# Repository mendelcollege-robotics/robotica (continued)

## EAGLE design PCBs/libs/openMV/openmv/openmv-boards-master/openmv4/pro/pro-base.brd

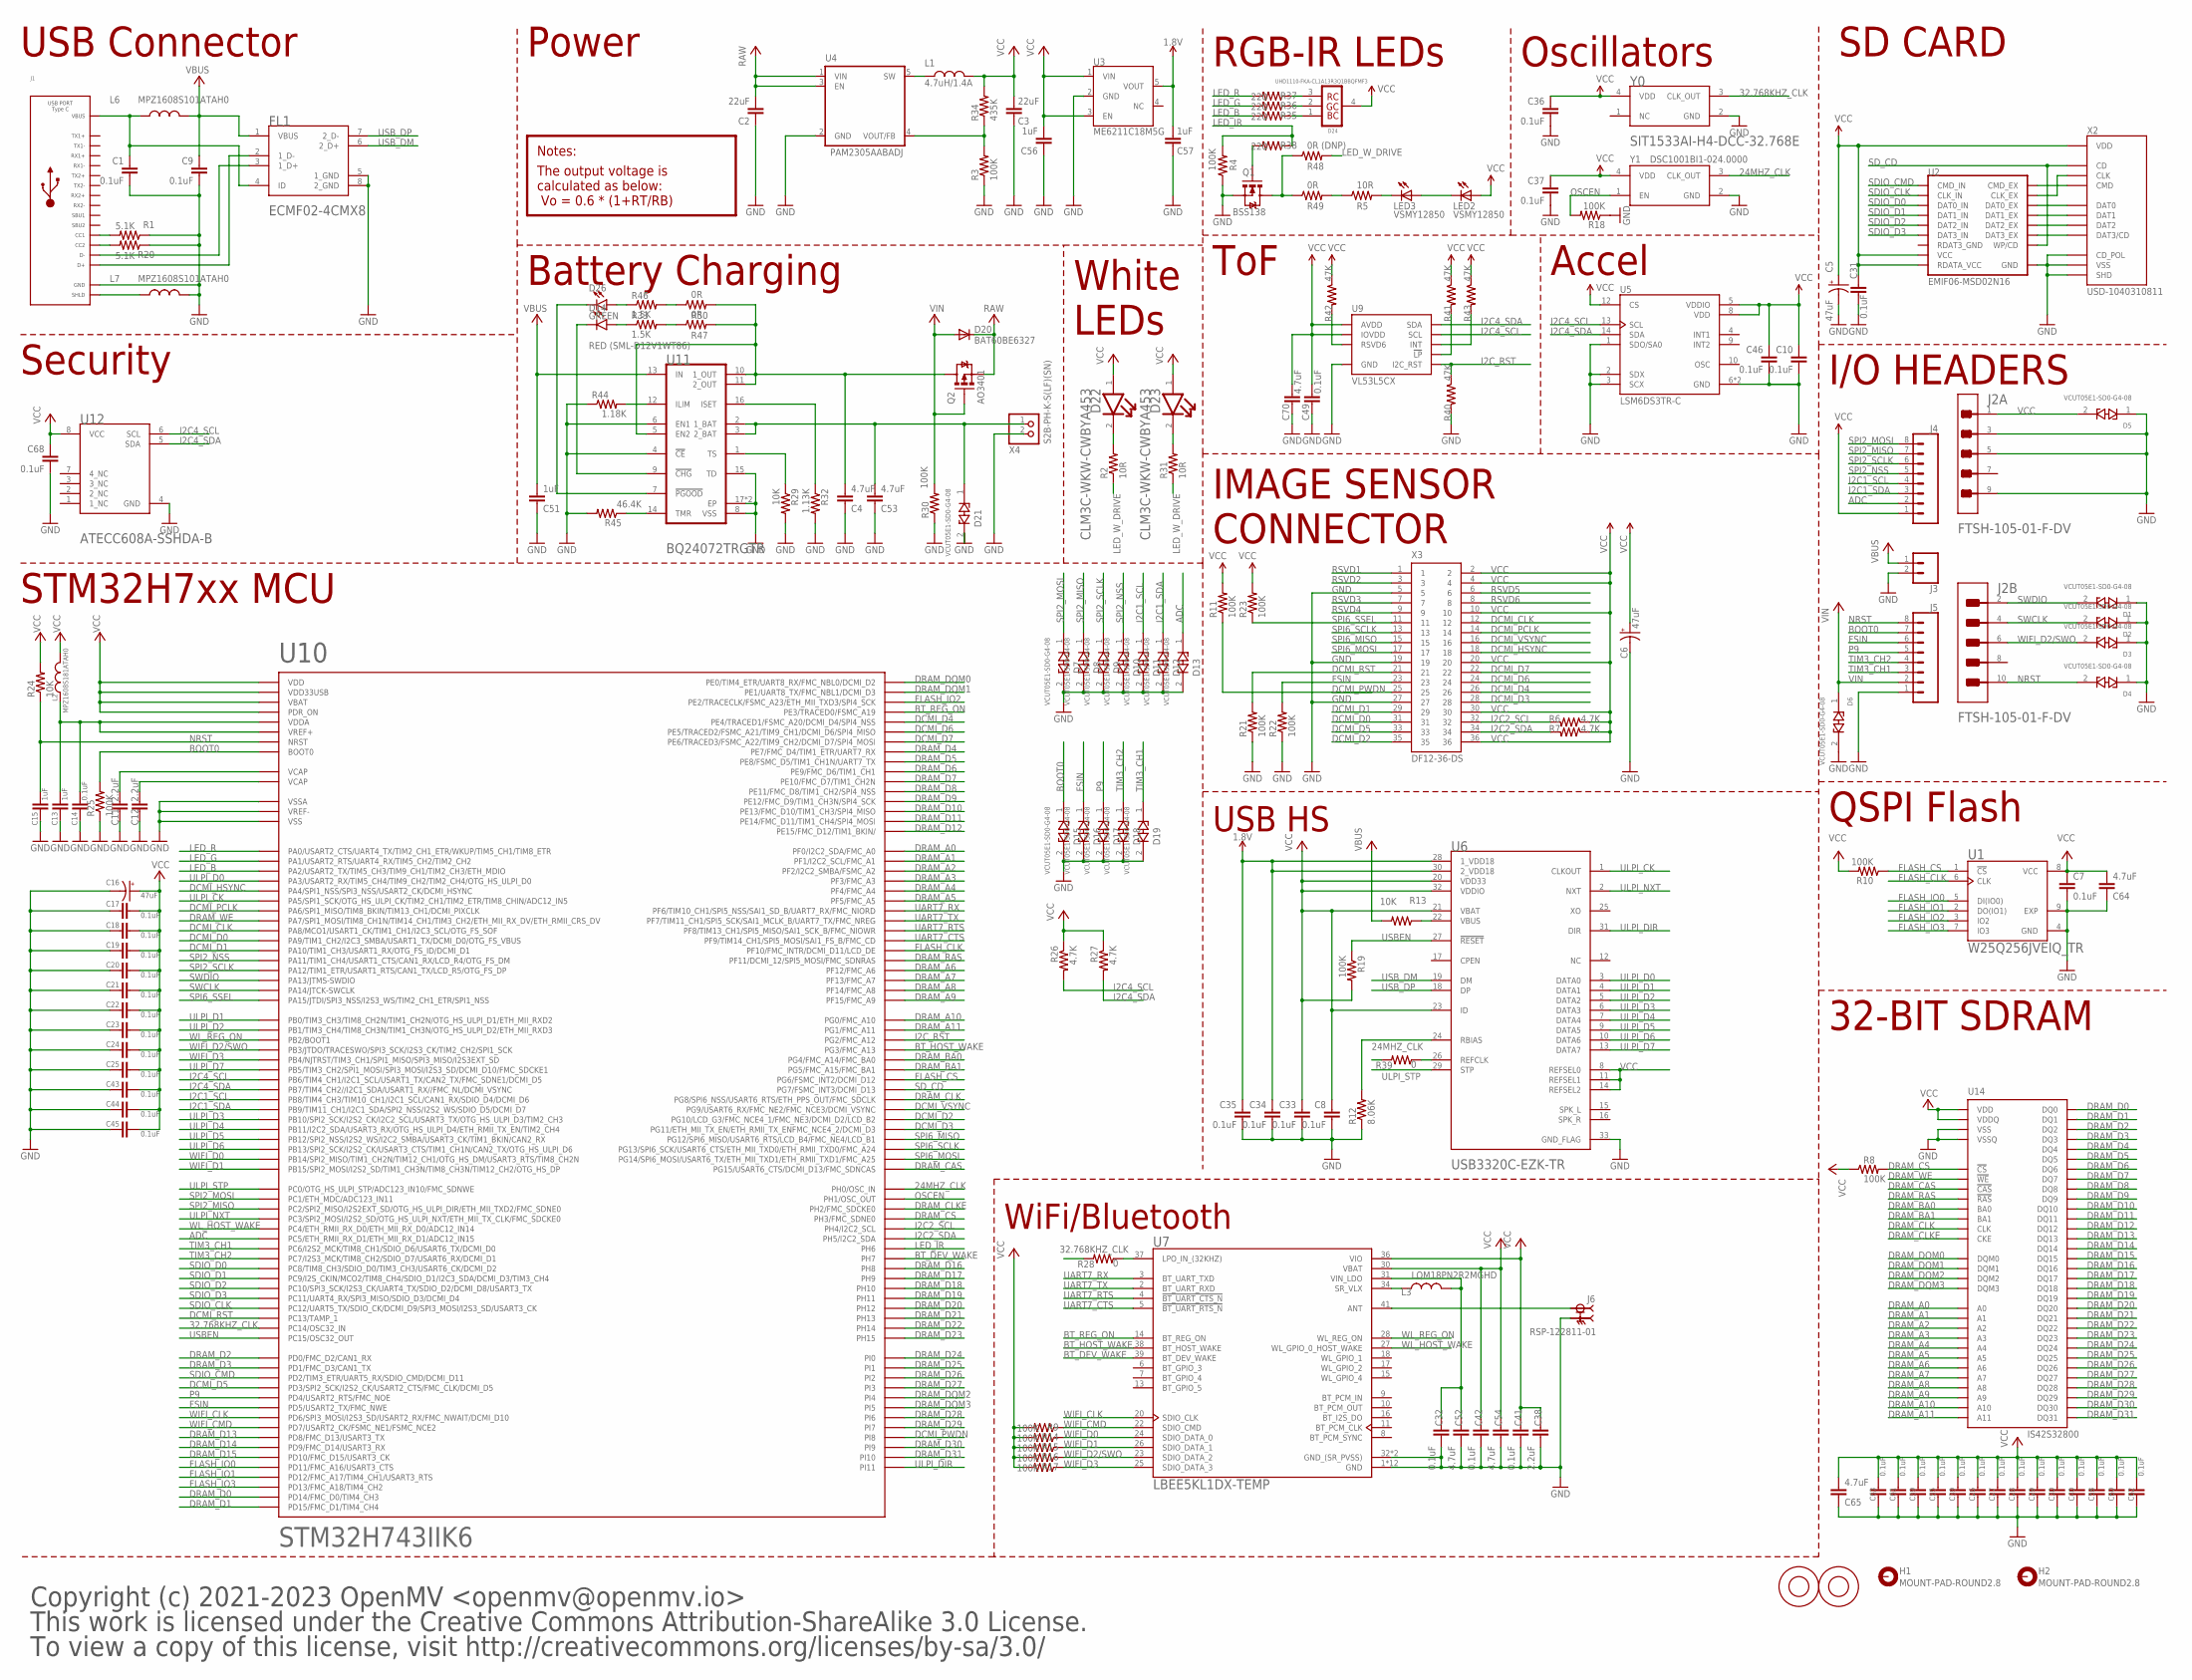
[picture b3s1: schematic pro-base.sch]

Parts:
C1, C7, C8, C9, C10, C14, C31, C32, C33, C34, C35, C36, C37, C41, C42, C46, C49, C68: 0.1uF; 0402-CAP
C2, C3: 22uF; 0805
C4, C52, C53, C54, C64, C65, C70: 4.7uF; 0603
C5, C6, C16: 47uF; EIA3216
C11, C12, C38: 2.2uF; 0402-CAP
C13, C15, C51, C56, C57: 1uF; 0402-CAP
C17, C18, C19, C20, C21, C22, C23, C24, C25, C26, C27, C28, C29, C30, C39, C40, C43, C44, C45, C55, C58, C59, C60, C61, C62, C63: 0.1uF; C0201
D1, D2, D3, D4, D5, D6, D7, D8, D9, D10, D11, D12, D13, D15, D16, D17, D18, D19, D21: VISHAY_VCUT05E1-SD0-G4-08VISHAY_VCUT05E1-SD0-G4-0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; VISHAY_VCUT05E1-SD0-G4-08_0
D14: RED (SML-D12V1WT86); LED-0603
D20: BAT60BE6327; SOD-323
D22, D23: CREE_CLM3C-WKW-CWBYA453CREE_CLM3C-WKW-CWBYA453_0_0; CREE_CLM3C-WKW-CWBYA453_0
D24: CREE_UHD1110-FKA-CL1A13R3Q1BBQFMF3CREE_UHD1110-FK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; CREE_UHD1110-FKA-CL1A13R3Q1BBQFMF3_0
D26: GREEN; LED-0603
FL1: STMICROELECTRONICS_ECMF02-4CMX8STMICROELECTRONICS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; STMICROELECTRONICS_ECMF02-4CMX8_0
H1, H2: MOUNT-PAD-ROUND2.8; 2,8-PAD
J1: USB_TYPE-C_105450-0101; 105450-0101
J2: SAMTEC_FTSH-105-01-F-DVSAMTEC_FTSH-105-01-F-DV_0_0; SAMTEC_FTSH-105-01-F-DV_0
J3: CONN_02; 1X02
J4, J5: CONN_08"; 1X08
J6: RSP-122811-01; SAMTEC_RSP-122811-01
L1: 4.7uH/1.4A; 1007
L2: MPZ1608S181ATAH0; C0402
L3: LQM18PN2R2MGHD; 0603
L6, L7: MPZ1608S101ATAH0; C0402
LED2, LED3: VSMY12850; LED-1206
M1, M2: 9774030243R; 9774030151R
Q1: BSS138; SOT23-3
Q2: AO3401; SOT23-3
R1, R20: 5.1K; 0402-RES
R2, R5, R31: 10R; 0402-RES
R3, R4, R8, R9, R10, R11, R14, R15, R16, R17, R18, R19, R21, R22, R23, R25, R30: 100K; 0402-RES
R6, R7, R26, R27: 4.7K; 0402-RES
R12: 8.06K; 0402-RES
R13, R24, R29: 10K; 0402-RES
R28, R39: 0; 0402-RES
R32: 1.13K; 0402-RES
R33, R46: 1.5K; 0402-RES
R34: 435K; 0402-RES
R35, R36, R37, R38: 220; 0402-RES
R40, R41, R42, R43: 47K; 0402-RES
R44: 1.18K; 0402-RES
R45: 46.4K; 0402-RES
R47, R49, R50: 0R; 0402-RES
R48: 0R (DNP); 0402-RES
U1: W25Q256JVEIQ_TR; SON127P800X600X80-9N
U2: EMIF06-MSD02N16; QFN3.5
U3: ME6211C18M5G; SOT23-5
U4: PAM2305AABADJ; TSOT25
U5: LSM6DS3TR-C; PQFN50P300X250X86-14N
U6: MICROCHIP_USB3320C-EZK-TRMICROCHIP_USB3320C-EZK-T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; MICROCHIP_USB3320C-EZK-TR_1
U7: LBEE5KL1DX-TEMP; XCVR_LBEE5KL1DX-TEMP
U9: VL53L5CX
U10: STM32H743IIK6; UFGBGA-176
U11: TEXAS_INSTRUMENTS_BQ24072TRGTRTEXAS_INSTRUMENTS_B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; TEXAS_INSTRUMENTS_BQ24072TRGTR_0
U12: MICROCHIP_ATECC608A-SSHDA-BMICROCHIP_ATECC608A-SS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; MICROCHIP_ATECC608A-SSHDA-B_0
U14: IS42S32800; BGA90
X2: USD-1040310811; 1040310811
X3: DF12-36-DS
X4: S2B-PH-K-S(LF)(SN); JST-PH-2-THM-RA
Y0: SITIME_SIT1533AI-H4-DCC-32.768ESITIME_SIT1533AI-H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; SITIME_SIT1533AI-H4-DCC-32.768E_0
Y1: DSC1001BI1-024.0000; OSC_DSC6083CI2A-032K768

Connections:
1.8V: C34.1, C35.1, C57.2, U3.5 (VOUT), U6.28 (1_VDD18), U6.30 (2_VDD18)
24MHZ_CLK: R39.2, U10.G1 (PH0/OSC_IN), Y1.3 (CLK_OUT)
32.768KHZ_CLK: R28.2, U10.E1 (PC14/OSC32_IN), Y0.3 (CLK_OUT)
ADC: D13.1, J4.2, U10.P5 (PC5/ETH_RMII_RX_D1/ETH_MII_RX_D1/ADC12_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)
ANT_PI_I: J6.1, U7.41 (ANT)
BAT: C53.2, D21.1, U11.2 (1_BAT), U11.3 (2_BAT), X4.1 (2)
BOOT0: D15.1, J5.7, R25.2, U10.D6 (BOOT0)
BT_DEV_WAKE: U7.39 (BT_DEV_WAKE), U10.N12 (PH7)
BT_HOST_WAKE: U7.38 (BT_HOST_WAKE), U10.K15 (PG3/FMC_A13)
BT_REG_ON: U7.14 (BT_REG_ON), U10.A1 (PE3/TRACED0/FSMC_A19)
CC1: J1.A5 (CC1), R1.2
CC2: J1.B5 (CC2), R20.2
CHG: D14.C, U11.9 (!CHG!)
CLK: U2.P$11 (CLK_EX), X2.P$5 (CLK)
CMD: U2.P$12 (CMD_EX), X2.P$3 (CMD)
DAT0: U2.P$10 (DAT0_EX), X2.P$7 (DAT0)
DAT1: U2.P$9 (DAT1_EX), X2.P$8 (DAT1)
DAT2: U2.P$14 (DAT2_EX), X2.P$1 (DAT2)
DAT3: U2.P$13 (DAT3_EX), X2.P$2 (DAT3/CD)
DCMI_CLK: U10.F15 (PA8/MCO1/USART1_CK/TIM1_CH1/I2C3_SCL/OT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), X3.12
DCMI_D0: U10.E15 (PA9/TIM1_CH2/I2C3_SMBA/USART1_TX/DCMI_D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), X3.31
DCMI_D1: U10.D15 (PA10/TIM1_CH3/USART1_RX/OTG_FS_ID/DCMI_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), X3.29
DCMI_D2: U10.B10 (PG10/LCD_G3/FMC_NCE4_1/FMC_NE3/DCMI_D2/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), X3.35
DCMI_D3: U10.B9 (PG11/ETH_MII_TX_EN/ETH_RMII_TX_ENFMC_NC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), X3.28
DCMI_D4: U10.B1 (PE4/TRACED1/FSMC_A20/DCMI_D4/SPI4_NSS), X3.26
DCMI_D5: U10.D11 (PD3/SPI2_SCK/I2S2_CK/USART2_CTS/FMC_CLK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), X3.33
DCMI_D6: U10.B2 (PE5/TRACED2/FSMC_A21/TIM9_CH1/DCMI_D6/S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), X3.24
DCMI_D7: U10.B3 (PE6/TRACED3/FSMC_A22/TIM9_CH2/DCMI_D7/S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), X3.22
DCMI_HSYNC: U10.N4 (PA4/SPI1_NSS/SPI3_NSS/USART2_CK/DCMI_HS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), X3.18
DCMI_PCLK: U10.P3 (PA6/SPI1_MISO/TIM8_BKIN/TIM13_CH1/DCMI_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), X3.14
DCMI_PWDN: R11.1, U10.D2 (PI8), X3.25
DCMI_RST: R21.2, U10.D1 (PC13/TAMP_1), X3.21
DCMI_VSYNC: U10.C10 (PG9/USART6_RX/FMC_NE2/FMC_NCE3/DCMI_VSY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), X3.16
DN: FL1.3 (1_D+), J1.A7 (D-), J1.B7 (D-)
DP: FL1.2 (1_D-), J1.A6 (D+), J1.B6 (D+)
DRAM_A0: U10.E2 (PF0/I2C2_SDA/FMC_A0), U14.G8 (A0)
DRAM_A1: U10.H3 (PF1/I2C2_SCL/FMC_A1), U14.G9 (A1)
DRAM_A2: U10.H2 (PF2/I2C2_SMBA/FSMC_A2), U14.F7 (A2)
DRAM_A3: U10.J2 (PF3/FMC_A3), U14.F3 (A3)
DRAM_A4: U10.J3 (PF4/FMC_A4), U14.G1 (A4)
DRAM_A5: U10.K3 (PF5/FMC_A5), U14.G2 (A5)
DRAM_A6: U10.P6 (PF12/FMC_A6), U14.G3 (A6)
DRAM_A7: U10.N6 (PF13/FMC_A7), U14.H1 (A7)
DRAM_A8: U10.R7 (PF14/FMC_A8), U14.H2 (A8)
DRAM_A9: U10.P7 (PF15/FMC_A9), U14.J3 (A9)
DRAM_A10: U10.N7 (PG0/FMC_A10), U14.G7 (A10)
DRAM_A11: U10.M7 (PG1/FMC_A11), U14.H9 (A11)
DRAM_BA0: U10.K14 (PG4/FMC_A14/FMC_BA0), U14.J7 (BA0)
DRAM_BA1: U10.K13 (PG5/FMC_A15/FMC_BA1), U14.H8 (BA1)
DRAM_CAS: U10.B7 (PG15/USART6_CTS/DCMI_D13/FMC_SDNCAS), U14.K7 (!CAS)
DRAM_CLK: U10.H14 (PG8/SPI6_NSS/USART6_RTS/ETH_PPS_OUT/FMC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), U14.J1 (CLK)
DRAM_CLKE: U10.F4 (PH2/FMC_SDCKE0), U14.J2 (CKE)
DRAM_CS: R8.2, U10.G4 (PH3/FMC_SDNE0), U14.J8 (!CS)
DRAM_D0: U10.M14 (PD14/FMC_D0/TIM4_CH3), U14.R8 (DQ0)
DRAM_D1: U10.L14 (PD15/FMC_D1/TIM4_CH4), U14.N7 (DQ1)
DRAM_D2: U10.B12 (PD0/FMC_D2/CAN1_RX), U14.R9 (DQ2)
DRAM_D3: U10.C12 (PD1/FMC_D3/CAN1_TX), U14.N8 (DQ3)
DRAM_D4: U10.R8 (PE7/FMC_D4/TIM1_ETR/UART7_RX), U14.P9 (DQ4)
DRAM_D5: U10.P8 (PE8/FSMC_D5/TIM1_CH1N/UART7_TX), U14.M8 (DQ5)
DRAM_D6: U10.P9 (PE9/FMC_D6/TIM1_CH1), U14.M7 (DQ6)
DRAM_D7: U10.R9 (PE10/FMC_D7/TIM1_CH2N), U14.L8 (DQ7)
DRAM_D8: U10.P10 (PE11/FMC_D8/TIM1_CH2/SPI4_NSS), U14.L2 (DQ8)
DRAM_D9: U10.R10 (PE12/FMC_D9/TIM1_CH3N/SPI4_SCK), U14.M3 (DQ9)
DRAM_D10: U10.N11 (PE13/FMC_D10/TIM1_CH3/SPI4_MISO), U14.M2 (DQ10)
DRAM_D11: U10.P11 (PE14/FMC_D11/TIM1_CH4/SPI4_MOSI), U14.P1 (DQ11)
DRAM_D12: U10.R11 (PE15/FMC_D12/TIM1_BKIN/), U14.N2 (DQ12)
DRAM_D13: U10.P15 (PD8/FMC_D13/USART3_TX), U14.R1 (DQ13)
DRAM_D14: U10.P14 (PD9/FMC_D14/USART3_RX), U14.N3 (DQ14)
DRAM_D15: U10.N15 (PD10/FMC_D15/USART3_CK), U14.R2 (DQ15)
DRAM_D16: U10.M12 (PH8), U14.E8 (DQ16)
DRAM_D17: U10.M13 (PH9), U14.D7 (DQ17)
DRAM_D18: U10.L13 (PH10), U14.D8 (DQ18)
DRAM_D19: U10.L12 (PH11), U14.B9 (DQ19)
DRAM_D20: U10.K12 (PH12), U14.C8 (DQ20)
DRAM_D21: U10.E12 (PH13), U14.A9 (DQ21)
DRAM_D22: U10.E13 (PH14), U14.C7 (DQ22)
DRAM_D23: U10.D13 (PH15), U14.A8 (DQ23)
DRAM_D24: U10.E14 (PI0), U14.A2 (DQ24)
DRAM_D25: U10.D14 (PI1), U14.C3 (DQ25)
DRAM_D26: U10.C14 (PI2), U14.A1 (DQ26)
DRAM_D27: U10.C13 (PI3), U14.C2 (DQ27)
DRAM_D28: U10.C3 (PI6), U14.B1 (DQ28)
DRAM_D29: U10.C2 (PI7), U14.D2 (DQ29)
DRAM_D30: U10.D3 (PI9), U14.D3 (DQ30)
DRAM_D31: U10.E3 (PI10), U14.E2 (DQ31)
DRAM_DQM0: U10.A4 (PE0/TIM4_ETR/UART8_RX/FMC_NBL0/DCMI_D2), U14.K9 (DQM0)
DRAM_DQM1: U10.A3 (PE1/UART8_TX/FMC_NBL1/DCMI_D3), U14.K1 (DQM1)
DRAM_DQM2: U10.D4 (PI4), U14.F8 (DQM2)
DRAM_DQM3: U10.C4 (PI5), U14.F2 (DQM3)
DRAM_RAS: U10.R6 (PF11/DCMI_12/SPI5_MOSI/FMC_SDNRAS), U14.J9 (!RAS)
DRAM_WE: U10.R3 (PA7/SPI1_MOSI/TIM8_CH1N/TIM14_CH1/TIM3_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), U14.K8 (!WE)
FB: R3.2, R34.1, U4.4 (VOUT/FB)
FLASH_CLK: U1.6 (CLK), U10.L1 (PF10/FMC_INTR/DCMI_D11/LCD_DE)
FLASH_CS: R10.1, U1.1 (!CS), U10.J15 (PG6/FSMC_INT2/DCMI_D12)
FLASH_IO0: U1.5 (DI(IO0)), U10.N14 (PD11/FMC_A16/USART3_CTS)
FLASH_IO1: U1.2 (DO(IO1)), U10.N13 (PD12/FMC_A17/TIM4_CH1/USART3_RTS)
FLASH_IO2: U1.3 (IO2), U10.A2 (PE2/TRACECLK/FSMC_A23/ETH_MII_TXD3/SPI4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)
FLASH_IO3: U1.7 (IO3), U10.M15 (PD13/FMC_A18/TIM4_CH2)
FSIN: D16.1, J5.6, R22.2, U10.C11 (PD5/USART2_TX/FMC_NWE), X3.23
GND: C1.2, C2.1, C3.1, C4.1, C5.C (-), C6.C (-), C7.2, C8.2, C9.2, C10.2, C11.2, C12.2, C13.2, C14.2, C15.2, C16.C (-), C17.2, C18.2, C19.2, C20.2, C21.2, C22.2, C23.2, C24.2, C25.2, C26.2, C27.2, C28.2, C29.2, C30.2, C31.2, C32.2, C33.2, C34.2, C35.2, C36.2, C37.2, C38.2, C39.2, C40.2, C41.2, C42.2, C43.2, C44.2, C45.2, C46.2, C49.2, C51.1, C52.2, C53.1, C54.2, C55.2, C56.1, C57.1, C58.2, C59.2, C60.2, C61.2, C62.2, C63.2, C64.1, C65.1, C68.2, C70.1, D1.1, D2.1, D3.1, D4.1, D5.1, D6.2, D7.2, D8.2, D9.2, D10.2, D11.2, D12.2, D13.2, D15.2, D16.2, D17.2, D18.2, D19.2, D21.2, FL1.5 (1_GND), FL1.8 (2_GND), J1.A1 (GND), J1.A12 (GND), J1.B1 (GND), J1.B12 (GND), J2.3, J2.5, J2.9, J3.2, J5.1, J6.G1 (GND), J6.G2 (GND), L7.2, Q1.2 (S), R1.1, R3.1, R4.1, R12.1, R18.1, R20.1, R21.1, R22.1, R25.1, R29.2, R30.1, R32.2, R40.2, R44.1, R45.2, U1.4 (GND), U1.9 (EXP), U2.GND, U3.2 (GND), U4.2 (GND), U5.1 (SDO/SA0), U5.2 (SDX), U5.3 (SCX), U5.6 (GND), U5.7 (GND), U6.33 (GND_FLAG), U7.1 (GND), U7.12 (GND)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
I2C1_SCL: D11.1, J4.4, U10.A5 (PB8/TIM4_CH3/TIM10_CH1/I2C1_SCL/CAN1_RX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)
I2C1_SDA: D12.1, J4.3, U10.B4 (PB9/TIM11_CH1/I2C1_SDA/SPI2_NSS/I2S2_WS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)
I2C2_SCL: R6.2, U10.H4 (PH4/I2C2_SCL), X3.32
I2C2_SDA: R7.2, U10.J4 (PH5/I2C2_SDA), X3.34
I2C4_SCL: R26.2, U5.13 (SCL), U9.C4 (SCL), U10.B6 (PB6/TIM4_CH1/I2C1_SCL/USART1_TX/CAN2_TX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), U12.6 (SCL)
I2C4_SDA: R27.2, U5.14 (SDA), U9.C3 (SDA), U10.B5 (PB7/TIM4_CH2//I2C1_SDA/USART1_RX//FMC_N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), U12.5 (SDA)
I2C_RST: R40.1, U9.A1 (I2C_RST), U10.L15 (PG2/FMC_A12)
ISET: R32.1, U11.16 (ISET)
LED_B: R35.2, U10.P2 (PA2/USART2_TX/TIM5_CH3/TIM9_CH1/TIM2_CH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)
LED_B_INT: D24.1 (BLUE_CATHODE), R35.1
LED_DRAIN: Q1.3 (D), R48.1, R49.1
LED_G: R36.2, U10.N2 (PA1/USART2_RTS/UART4_RX/TIM5_CH2/TIM2_C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)
LED_G_INT: D24.2 (GREEN_CATHODE), R36.1
LED_IR: R4.2, R38.1, U10.M11 (PH6)
LED_IR_DRIVE: R5.1, R49.2
LED_IR_DRIVE_0: LED3.C, R5.2
LED_IR_DRIVE_1: LED2.C, LED3.A
LED_IR_INT: Q1.1 (G), R38.2
LED_R: R37.2, U10.N3 (PA0/USART2_CTS/UART4_TX/TIM2_CH1_ETR/WK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)
LED_R_INT: D24.3 (RED_CATHODE), R37.1
LED_W_DRIVE: R2.1, R31.1, R48.2
LED_W_DRIVE_0: D22.2 (CATHODE), R2.2
LED_W_DRIVE_1: D23.2 (CATHODE), R31.2
unnamed: D26.A, R46.1
unnamed: R28.1, U7.37 (LPO_IN_(32KHZ))
unnamed: R39.1, U6.26 (REFCLK)
unnamed: R44.2, U11.12 (ILIM)
unnamed: R41.2, U9.A5 (!LP)
unnamed: R42.2, U9.C2 (RSVD6)
unnamed: R43.2, U9.A3 (INT)
unnamed: R45.1, U11.14 (TMR)
unnamed: D26.C, U11.7 (!PGOOD!)
unnamed: D14.A, R33.1
unnamed: R33.2, R47.1
unnamed: R46.2, R50.1
NRST: C15.1, D4.2, J2.10, J5.8, R24.1, U10.J1 (NRST)
OSCEN: R18.2, U10.H1 (PH1/OSC_OUT), Y1.1 (EN)
OUT: C4.2, Q2.3 (D), R47.2, R50.2, U11.5 (EN2), U11.10 (1_OUT), U11.11 (2_OUT)
P9: D17.1, J5.5, U10.D10 (PD4/USART2_RTS/FMC_NOE)
RAW: C2.2, D20.1 (C), Q2.2 (S), U4.1 (VIN), U4.3 (EN)
RBIAS: R12.2, U6.24 (RBIAS)
RSVD1: X3.1
RSVD2: X3.3
RSVD3: X3.7
RSVD4: X3.9
RSVD5: X3.6
RSVD6: X3.8
SDIO_CLK: U2.P$6 (CLK_IN), U10.A12 (PC12/UART5_TX/SDIO_CK/DCMI_D9/SPI3_MOSI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)
SDIO_CMD: U2.P$5 (CMD_IN), U10.D12 (PD2/TIM3_ETR/UART5_RX/SDIO_CMD/DCMI_D11)
SDIO_D0: U2.P$7 (DAT0_IN), U10.G14 (PC8/TIM8_CH3/SDIO_D0/TIM3_CH3/USART6_CK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)
SDIO_D1: U2.P$8 (DAT1_IN), U10.F14 (PC9/I2S_CKIN/MCO2/TIM8_CH4/SDIO_D1/I2C3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)
SDIO_D2: U2.P$3 (DAT2_IN), U10.B14 (PC10/SPI3_SCK/I2S3_CK/UART4_TX/SDIO_D2/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)
SDIO_D3: U2.P$4 (DAT3_IN), U10.B13 (PC11/UART4_RX/SPI3_MISO/SDIO_D3/DCMI_D4)
SD_CD: U2.P$1 (WP/CD), U10.J14 (PG7/FSMC_INT3/DCMI_D13), X2.CD$1 (CD)
SHIELD_INT: J1.S_T1 (SHLD), J1.S_T2 (SHLD), J1.S_T3 (SHLD), J1.S_T4 (SHLD), L7.1
SPI2_MISO: D8.1, J4.7, U10.M4 (PC2/SPI2_MISO/I2S2EXT_SD/OTG_HS_ULPI_DI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)
SPI2_MOSI: D7.1, J4.8, U10.M3 (PC1/ETH_MDC/ADC123_IN11)
SPI2_NSS: D10.1, J4.5, U10.C15 (PA11/TIM1_CH4/USART1_CTS/CAN1_RX/LCD_R4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)
SPI2_SCLK: D9.1, J4.6, U10.B15 (PA12/TIM1_ETR/USART1_RTS/CAN1_TX/LCD_R5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)
SPI6_MISO: U10.B8 (PG12/SPI6_MISO/USART6_RTS/LCD_B4/FMC_NE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), X3.15
SPI6_MOSI: U10.A7 (PG14/SPI6_MOSI/USART6_TX/ETH_MII_TXD1/E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), X3.17
SPI6_SCLK: U10.A8 (PG13/SPI6_SCK/USART6_CTS/ETH_MII_TXD0/E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), X3.13
SPI6_SSEL: R23.1, U10.A13 (PA15/JTDI/SPI3_NSS/I2S3_WS/TIM2_CH1_ETR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), X3.11
SR)VLX: L3.1, U7.34 (SR_VLX)
SW: L1.1, U4.5 (SW)
SWCLK: D2.2, J2.4, U10.A14 (PA14/JTCK-SWCLK)
SWDIO: D1.2, J2.2, U10.A15 (PA13/JTMS-SWDIO)
TIM3_CH1: D19.1, J5.3, U10.H15 (PC6/I2S2_MCK/TIM8_CH1/SDIO_D6/USART6_TX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)
TIM3_CH2: D18.1, J5.4, U10.G15 (PC7/I2S3_MCK/TIM8_CH2/SDIO_D7/USART6_RX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)
TS: R29.1, U11.1 (TS)
UART7_CTS: U7.5 (!BT_UART_RTS_N), U10.L2 (PF9/TIM14_CH1/SPI5_MOSI/SAI1_FS_B/FMC_CD)
UART7_RTS: U7.4 (!BT_UART_CTS_N), U10.L3 (PF8/TIM13_CH1/SPI5_MISO/SAI1_SCK_B/FMC_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)
UART7_RX: U7.3 (BT_UART_TXD), U10.K2 (PF6/TIM10_CH1/SPI5_NSS/SAI1_SD_B/UART7_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)
UART7_TX: U7.2 (BT_UART_RXD), U10.K1 (PF7/TIM11_CH1/SPI5_SCK/SAI1_MCLK_B/UART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)
ULPI_CK: U6.1 (CLKOUT), U10.P4 (PA5/SPI1_SCK/OTG_HS_ULPI_CK/TIM2_CH1/TI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)
ULPI_D0: U6.3 (DATA0), U10.R2 (PA3/USART2_RX/TIM5_CH4/TIM9_CH2/TIM2_CH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)
ULPI_D1: U6.4 (DATA1), U10.R5 (PB0/TIM3_CH3/TIM8_CH2N/TIM1_CH2N/OTG_HS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)
ULPI_D2: U6.5 (DATA2), U10.R4 (PB1/TIM3_CH4/TIM8_CH3N/TIM1_CH3N/OTG_HS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)
ULPI_D3: U6.6 (DATA3), U10.R12 (PB10/SPI2_SCK/I2S2_CK/I2C2_SCL/USART3_T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)
ULPI_D4: U6.7 (DATA4), U10.R13 (PB11/I2C2_SDA/USART3_RX/OTG_HS_ULPI_D4/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)
ULPI_D5: U6.9 (DATA5), U10.P12 (PB12/SPI2_NSS/I2S2_WS/I2C2_SMBA/USART3_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)
ULPI_D6: U6.10 (DATA6), U10.P13 (PB13/SPI2_SCK/I2S2_CK/USART3_CTS/TIM1_C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)
ULPI_D7: U6.13 (DATA7), U10.A6 (PB5/TIM3_CH2/SPI1_MOSI/SPI3_MOSI/I2S3_S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)
ULPI_DIR: U6.31 (DIR), U10.E4 (PI11)
ULPI_NXT: U6.2 (NXT), U10.M5 (PC3/SPI2_MOSI/I2S2_SD/OTG_HS_ULPI_NXT/E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)
ULPI_STP: U6.29 (STP), U10.M2 (PC0/OTG_HS_ULPI_STP/ADC123_IN10/FMC_SDN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)
USBEN: R19.1, U6.27 (!RESET!), U10.F1 (PC15/OSC32_OUT)
USB_DM: FL1.6 (2_D+), U6.19 (DM)
USB_DP: FL1.7 (2_D-), U6.18 (DP)
VBUS: C9.1, C51.2, FL1.1 (VBUS), J3.1, L6.2, R13.2, U11.13 (IN)
VBUS_INT: C1.1, FL1.4 (ID), J1.A4 (VBUS), J1.A9 (VBUS), J1.B4 (VBUS), J1.B9 (VBUS), L6.1
VBUS_SENSE: R13.1, U6.22 (VBUS)
VCAP1: C11.1, U10.F13 (VCAP)
VCAP2: C12.1, U10.M10 (VCAP)
VCC: C3.2, C5.A (+), C6.A (+), C7.1, C8.1, C10.1, C16.A (+), C17.1, C18.1, C19.1, C20.1, C21.1, C22.1, C23.1, C24.1, C25.1, C26.1, C27.1, C28.1, C29.1, C30.1, C31.1, C33.1, C36.1, C37.1, C38.1, C39.1, C40.1, C41.1, C42.1, C43.1, C44.1, C45.1, C46.1, C49.1, C54.1, C55.1, C56.2, C58.1, C59.1, C60.1, C61.1, C62.1, C63.1, C64.2, C65.2, C68.1, C70.2, D5.2, D22.1 (ANODE), D23.1 (ANODE), D24.4 (COMMON_ANODE), J2.1, J4.1, L1.2, L2.2, LED2.A, R6.1, R7.1, R8.1, R9.2, R10.2, R11.2, R14.2, R15.2, R16.2, R17.2, R19.2, R23.2, R24.2, R26.1, R27.1, R34.2, R41.1, R42.1, R43.1, U1.8 (VCC), U2.P$15 (VCC), U2.P$16 (RDATA_VCC), U3.1 (VIN), U3.3 (EN), U5.5 (VDDIO), U5.8 (VDD), U5.12 (CS), U6.8 (REFSEL0), U6.11 (REFSEL1), U6.14 (REFSEL2), U6.20 (VDD33), U6.21 (VBAT), U6.23 (ID), U6.32 (VDDIO), U7.30 (VBAT), U7.36 (VIO), U9.A4 (IOVDD), U9.B1 (AVDD), U9.B7 (AVDD), U10.C1 (VBAT), U10.C5 (VDD), U10.C6 (PDR_ON), U10.C7 (VDD), U10.C8 (VDD), U10.C9 (VDD), U10.F3 (VDD), U10.G3 (VDD), U10.G13 (VDD), U10.H13 (VDD33USB), U10.J12 (VDD), U10.J13 (VDD), U10.K4 (VDD), U10.N8 (VDD), U10.N9 (VDD), U10.N10 (VDD), U12.8 (VCC), U14.A7 (VDD), U14.B2 (VDDQ), U14.B7 (VDDQ), U14.C9 (VDDQ), U14.D9 (VDDQ), U14.E1 (VDDQ), U14.F9 (VDD), U14.L1 (VDDQ), U14.L7 (VDD), U14.M9 (VDDQ), U14.N9 (VDDQ), U14.P2 (VDDQ), U14.P7 (VDDQ)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
VDDA: C13.1, C14.1, L2.1, U10.P1 (VREF+), U10.R1 (VDDA)
VIN: D6.1, D20.2 (A), J5.2, Q2.1 (G), R30.2
VIN_LDO: C32.1, C52.1, L3.2, U7.31 (VIN_LDO)
WIFI_CLK: U7.20 (SDIO_CLK), U10.B11 (PD6/SPI3_MOSI/I2S3_SD/USART2_RX/FMC_NWA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)
WIFI_CMD: R9.1, U7.22 (SDIO_CMD), U10.A11 (PD7/USART2_CK/FSMC_NE1/FSMC_NCE2)
WIFI_D0: R14.1, U7.24 (SDIO_DATA_0), U10.R14 (PB14/SPI2_MISO/TIM1_CH2N/TIM12_CH1/OTG_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)
WIFI_D1: R15.1, U7.26 (SDIO_DATA_1), U10.R15 (PB15/SPI2_MOSI/I2S2_SD/TIM1_CH3N/TIM8_C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)
WIFI_D2/SWO: D3.2, J2.6, R16.1, U7.23 (SDIO_DATA_2), U10.A10 (PB3/JTDO/TRACESWO/SPI3_SCK/I2S3_CK/TIM2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)
WIFI_D3: R17.1, U7.25 (SDIO_DATA_3), U10.A9 (PB4/NJTRST/TIM3_CH1/SPI1_MISO/SPI3_MISO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)
WL_HOST_WAKE: U7.27 (WL_GPIO_0_HOST_WAKE), U10.N5 (PC4/ETH_RMII_RX_D0/ETH_MII_RX_D0/ADC12_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)
WL_REG_ON: U7.28 (WL_REG_ON), U10.M6 (PB2/BOOT1)

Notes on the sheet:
SD CARD
IMAGE SENSOR CONNECTOR
STM32H7xx MCU
RGB-IR LEDs
USB Connector
I/O HEADERS
The output voltage is calculated as below: Vo = 0.6 * (1+RT/RB)
Notes:
32-BIT SDRAM
QSPI Flash
WiFi/Bluetooth
USB HS
Oscillators
Copyright (c) 2021-2023 OpenMV <openmv@openmv.io>
This work is licensed under the Creative Commons Attribution-ShareAlike 3.0 License.
To view a copy of this license, visit http://creativecommons.org/licenses/by-sa/3.0/
Accel
Security
Battery Charging
Power
White LEDs
ToF

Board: 6 copper layers, 180 parts (104 on the bottom side), 200 nets, no tracks yet.

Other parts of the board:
U$1: WEEE
U$2: ROHS
U$3: OMV-LOGO
U$4: OMV-LOGO-SMALL

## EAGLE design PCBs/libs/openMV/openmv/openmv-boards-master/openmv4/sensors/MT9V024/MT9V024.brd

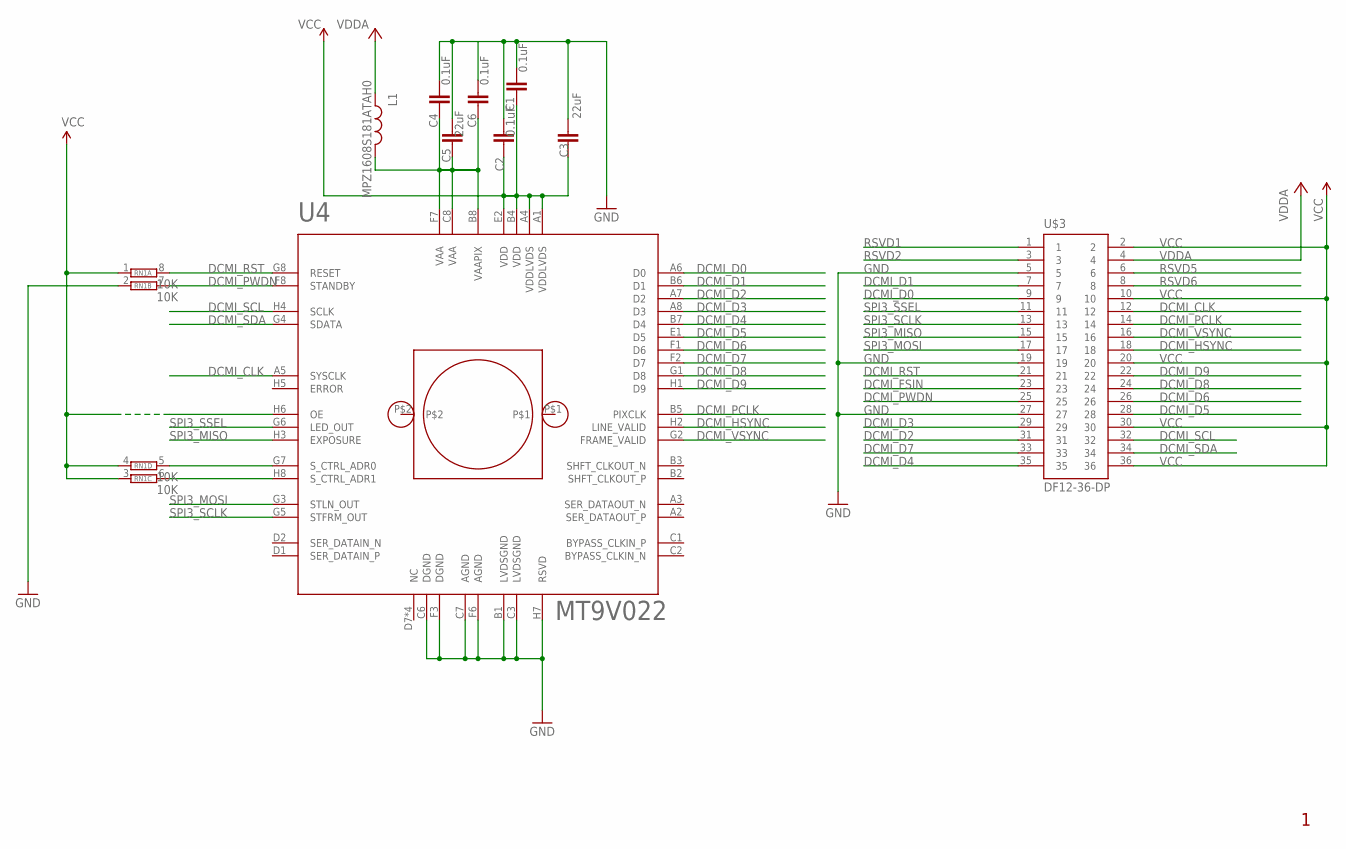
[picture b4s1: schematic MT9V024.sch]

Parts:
C1, C2, C4, C6: 0.1uF; 0402-CAP
C3, C5: 22uF; 0805
L1: MPZ1608S181ATAH0; 0603
LM1: LENSMOUNT20MM; LENSMOUNT-20MM
RN1: 10K; EXBV8V
U4: MT9V022; IBGA52
U$3: DF12-36-DP

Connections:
DCMI_CLK: U4.A5 (SYSCLK), U$3.12
DCMI_D0: U4.A6 (D0), U$3.9
DCMI_D1: U4.B6 (D1), U$3.7
DCMI_D2: U4.A7 (D2), U$3.31
DCMI_D3: U4.A8 (D3), U$3.29
DCMI_D4: U4.B7 (D4), U$3.35
DCMI_D5: U4.E1 (D5), U$3.28
DCMI_D6: U4.F1 (D6), U$3.26
DCMI_D7: U4.F2 (D7), U$3.33
DCMI_D8: U4.G1 (D8), U$3.24
DCMI_D9: U4.H1 (D9), U$3.22
DCMI_FSIN: U$3.23
DCMI_HSYNC: U4.H2 (LINE_VALID), U$3.18
DCMI_PCLK: U4.B5 (PIXCLK), U$3.14
DCMI_PWDN: RN1.7 (2), U4.F8 (STANDBY), U$3.25
DCMI_RST: RN1.8 (2), U4.G8 (RESET), U$3.21
DCMI_SCL: U4.H4 (SCLK), U$3.32
DCMI_SDA: U4.G4 (SDATA), U$3.34
DCMI_VSYNC: U4.G2 (FRAME_VALID), U$3.16
GND: C1.2, C2.2, C3.1, C4.2, C5.1, C6.2, RN1.2 (1), U4.B1 (LVDSGND), U4.C3 (LVDSGND), U4.C6 (DGND), U4.C7 (AGND), U4.F3 (DGND), U4.F6 (AGND), U4.H7 (RSVD), U$3.5, U$3.19, U$3.27
unnamed: RN1.5 (2), U4.G7 (S_CTRL_ADR0)
unnamed: RN1.6 (2), U4.H8 (S_CTRL_ADR1)
RSVD1: U$3.1
RSVD2: U$3.3
RSVD5: U$3.6
RSVD6: U$3.8
SPI3_MISO: U4.H3 (EXPOSURE), U$3.15
SPI3_MOSI: U4.G3 (STLN_OUT), U$3.17
SPI3_SCLK: U4.G5 (STFRM_OUT), U$3.13
SPI3_SSEL: U4.G6 (LED_OUT), U$3.11
VAA: C4.1, C5.2, C6.1, L1.2, U4.B8 (VAAPIX), U4.C8 (VAA), U4.F7 (VAA)
VCC: C1.1, C2.1, C3.2, RN1.1, RN1.3 (1), RN1.4 (1), U4.A1 (VDDLVDS), U4.A4 (VDDLVDS), U4.B4 (VDD), U4.E2 (VDD), U4.H6 (OE), U$3.2, U$3.10, U$3.20, U$3.30, U$3.36
VDDA: L1.1, U$3.4

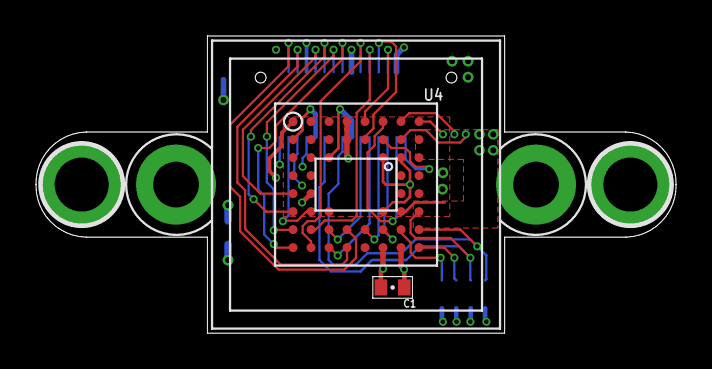
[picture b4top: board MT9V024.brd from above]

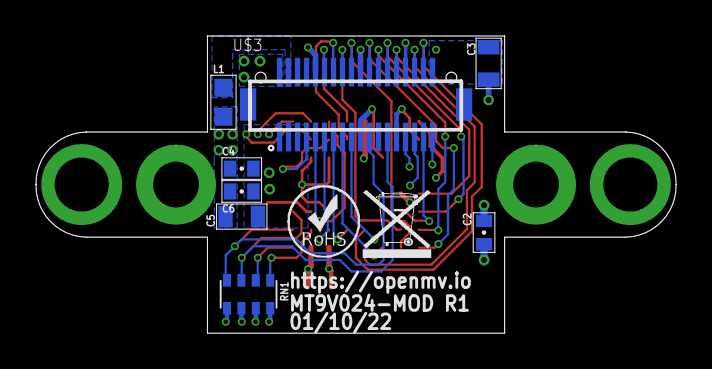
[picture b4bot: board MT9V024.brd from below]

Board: 4 copper layers, 35.6 x 16.5 mm, 13 parts (10 on the bottom side), 28 nets.

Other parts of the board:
U$1: WEEE
U$2: ROHS

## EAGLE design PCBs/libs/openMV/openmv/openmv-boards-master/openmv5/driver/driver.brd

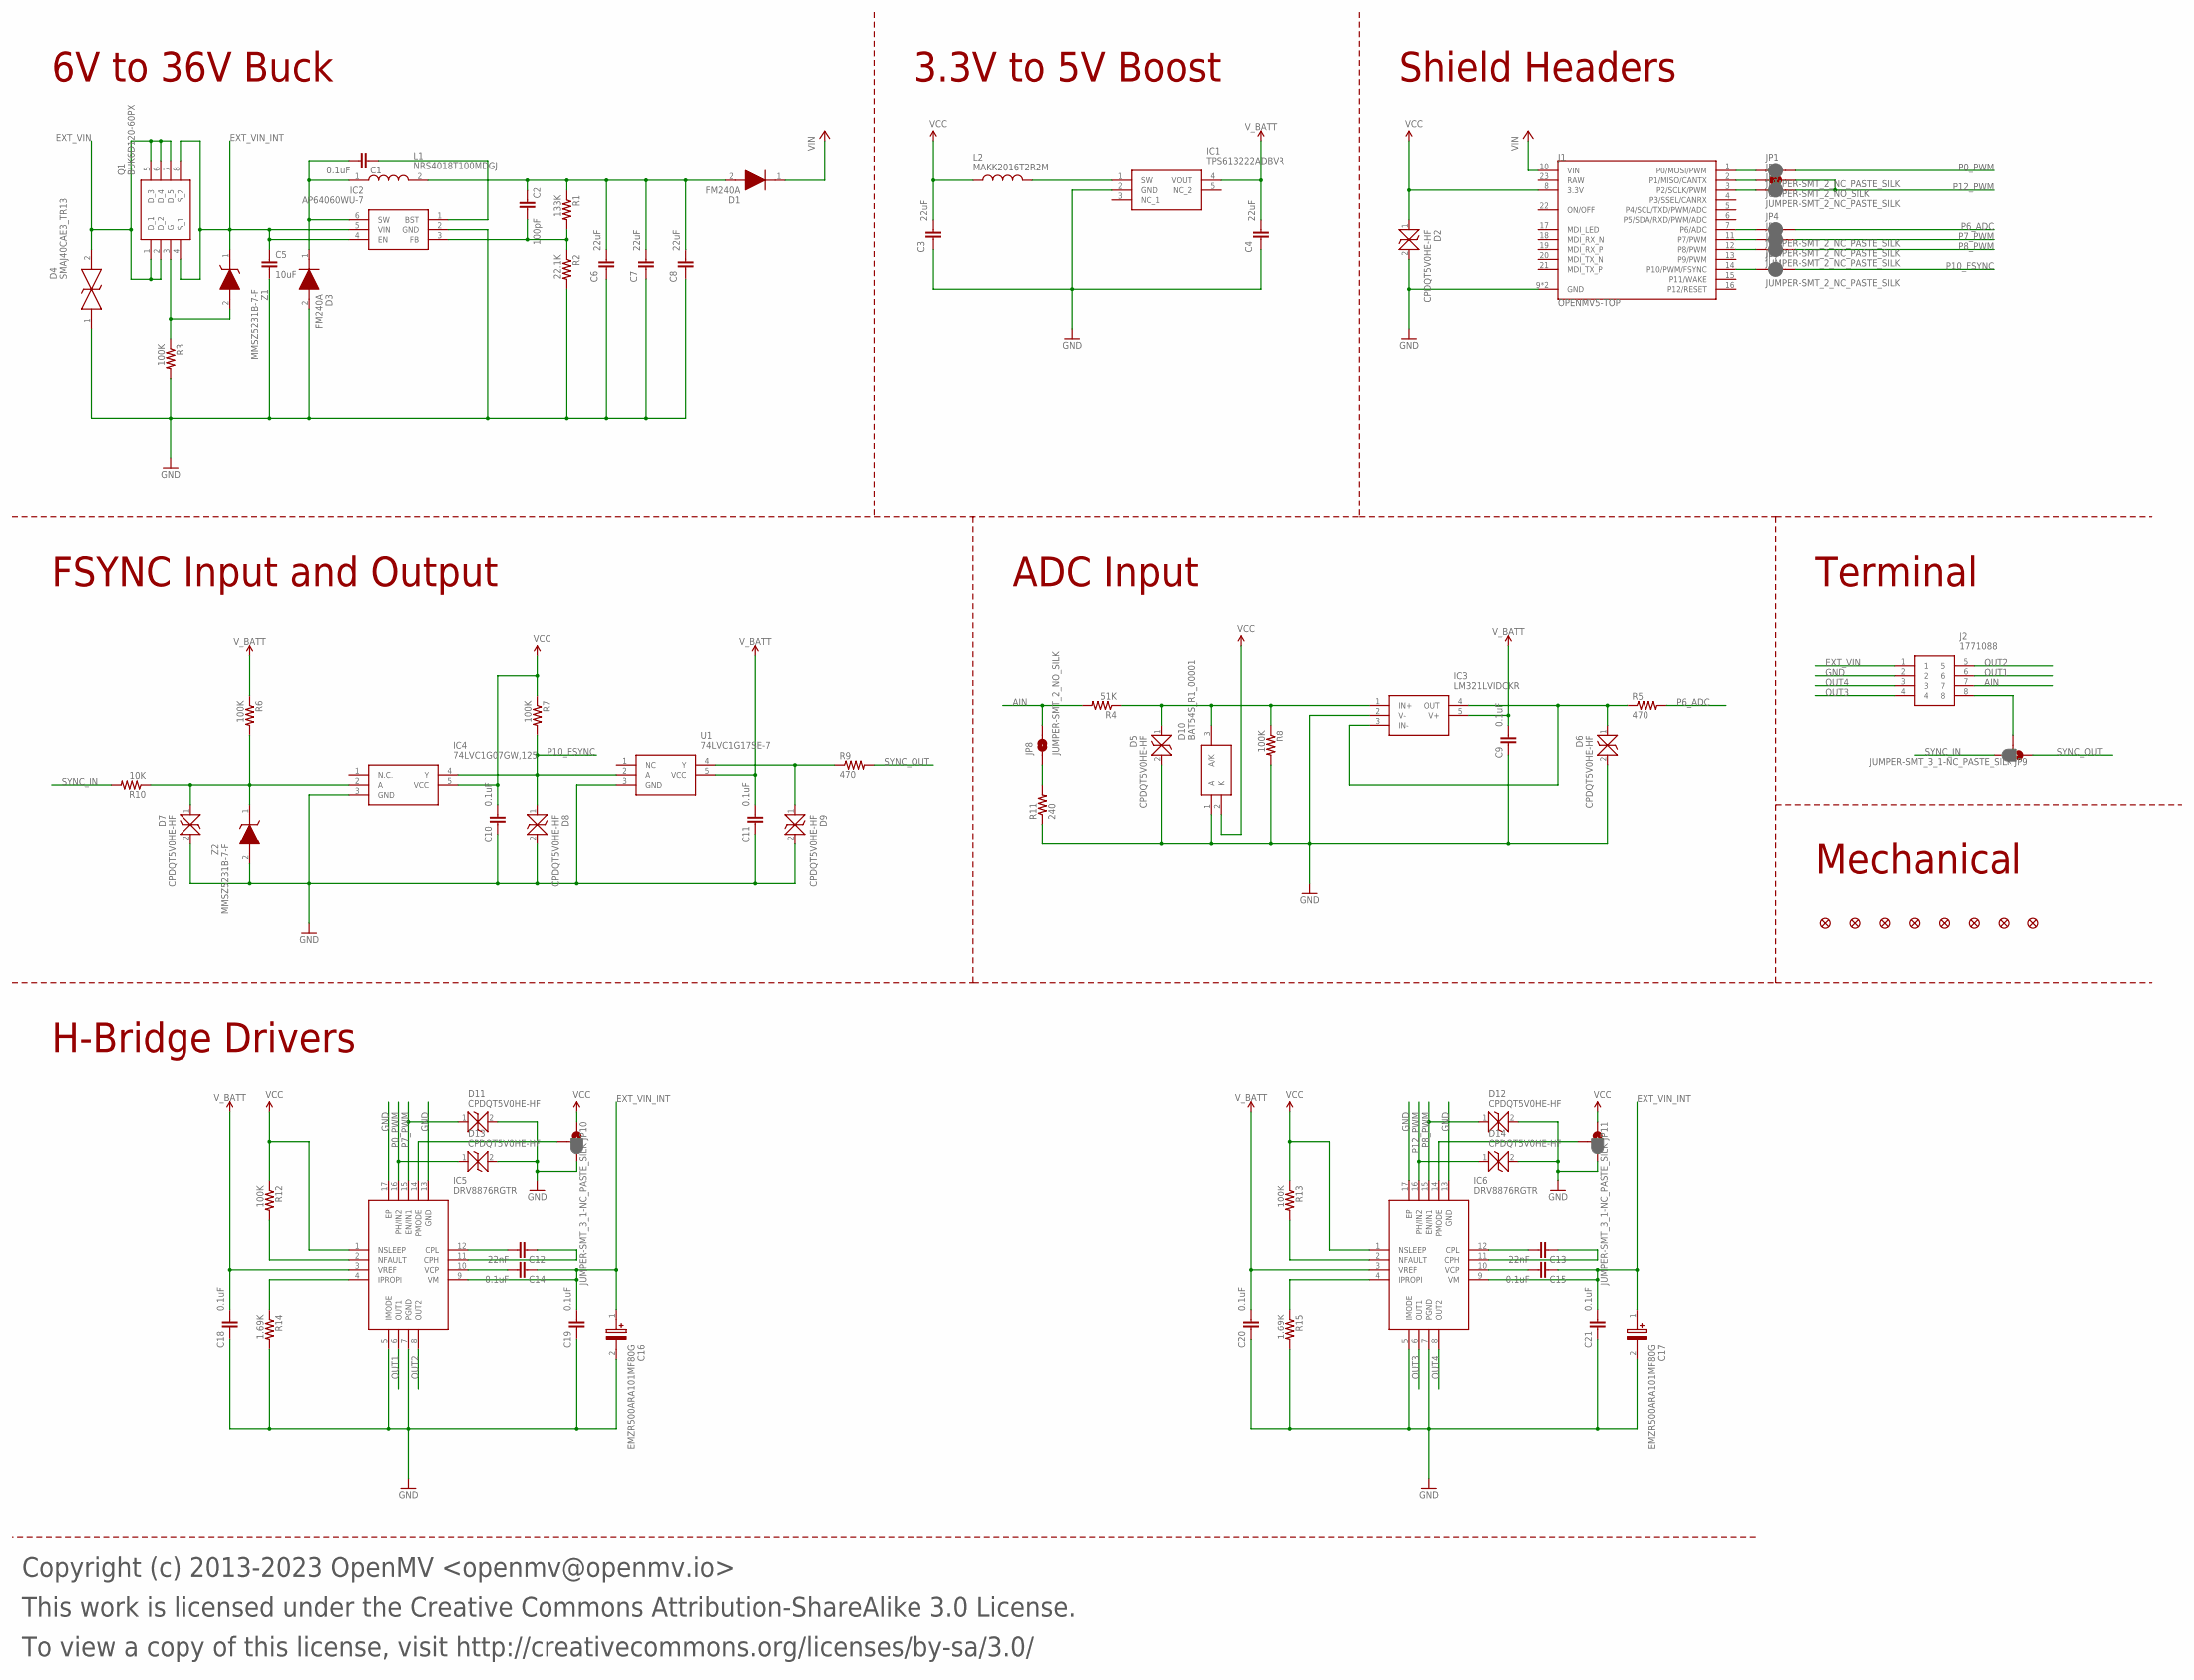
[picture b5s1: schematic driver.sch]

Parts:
C1, C9, C10, C11, C14, C15, C18, C19, C20, C21: 0.1uF; 0402-CAP; MPN GRM155R71H104KE14D
C2: 100pF; 0402-CAP; MPN CC0402JRNPO9BN101
C3, C4, C6, C7, C8: 22uF; 0805; MPN CL21A226MQQNNNE
C5: 10uF; C0805; MPN GRM21BR61H106KE43K
C12, C13: 22nF; 0402-CAP; MPN GRM155R71H223KA12D
C16, C17: EMZR500ARA101MF80G; CAPAE660X820N; MPN EMZR500ARA101MF80G
D1, D3: FM240A; DIOM5025X231N; MPN FM240A
D2, D5, D6, D7, D8, D9, D11, D12, D13, D14: CPDQT5V0HE-HF; CPDQT5V0HEHF; MPN CPDQT5V0HE-HF
D4: SMAJ40CAE3_TR13; SMAJ40CAE3TR13; MPN SMAJ40CAe3/TR13
D10: BAT54S_R1_00001; SOT95P240X110-3N; MPN BAT54S_R1_00001
FD1, FD2, FD3, FD4, FD5, FD6, FD7, FD8: FIDUCIAL1X2; FIDUCIAL-1X2
IC1: TPS613222ADBVR; SOT95P280X145-5N; MPN TPS613222ADBVR
IC2: AP64060WU-7; SOT95P280X100-6N; MPN AP64060WU-7
IC3: LM321LVIDCKR; SOT65P210X110-5N; MPN LM321LVIDCKR
IC4: 74LVC1G07GW,125; SOT65P212X110-5N; MPN 74LVC1G07GW,125
IC5, IC6: DRV8876RGTR; QFN50P300X300X100-17N; MPN DRV8876RGTR
J1: OPENMV5-TOP
J2: 1771088; MPN 1771088
JP1, JP3, JP4, JP5, JP6, JP7: JUMPER-SMT_2_NC_PASTE_SILK; SMT-JUMPER_2_NC_PASTE_SILK
JP2, JP8: JUMPER-SMT_2_NO_SILK; SMT-JUMPER_2_NO_SILK
JP9, JP10, JP11: JUMPER-SMT_3_1-NC_PASTE_SILK; SMT-JUMPER_3_1-NC_PASTE_SILK
L1: NRS4018T100MDGJ; MPN NRS4018T100MDGJ
L2: MAKK2016T2R2M; INDC2016X100N; MPN MAKK2016T2R2M
Q1: BUK6D120-60PX; BUK6D12060PX; MPN BUK6D120-60PX
R1: 133K; 0402-RES; MPN RC0402FR-07133KL
R2: 22.1K; 0402-RES; MPN CR0402-FX-2212GLF
R3, R6, R7, R8, R12, R13: 100K; 0402-RES; MPN AC0402FR-07100KL
R4: 51K; 0402-RES; MPN RC0402JR-0751KL
R5, R9: 470; R0603; MPN CR0603-FX-4700ELF
R10: 10K; 0402-RES; MPN AC0402FR-1310KL
R11: 240; R0603; MPN RK73B1JTTD241J
R14, R15: 1.69K; 0402-RES; MPN RC0402FR-07169RL
U1: 74LVC1G17SE-7; SOT65P210X110-5N; MPN 74LVC1G17SE-7
Z1, Z2: MMSZ5231B-7-F; SOD3716X145N; MPN MMSZ5231B-7-F

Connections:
AIN: J2.7, JP8.2, R4.2
AIN_INT: D5.1, D10.3 (A/K), IC3.1 (IN+), R4.1, R8.1
AIN_OUT: D6.1, IC3.3 (IN-), IC3.4 (OUT), R5.1
AIN_S: JP8.1, R11.2
CPH0: C12.1, IC5.11 (CPH)
CPH1: C13.1, IC6.11 (CPH)
CPL0: C12.2, IC5.12 (CPL)
CPL1: C13.2, IC6.12 (CPL)
EXT_VIN: D4.2, J2.1, Q1.1 (D_1), Q1.2 (D_2), Q1.5 (D_3), Q1.6 (D_4), Q1.7 (D_5)
EXT_VIN_BST: C1.1, IC2.1 (BST)
EXT_VIN_FB: C2.2, IC2.3 (FB), R1.2, R2.1
EXT_VIN_G: Q1.3 (G), R3.1, Z1.2 (A)
EXT_VIN_INT: C5.1, C14.1, C15.1, C16.1 (+), C17.1 (+), C19.2, C21.2, IC2.4 (EN), IC2.5 (VIN), IC5.9 (VM), IC6.9 (VM), Q1.4 (S_1), Q1.8 (S_2), Z1.1 (K)
EXT_VIN_OUT: C2.1, C6.2, C7.2, C8.2, D1.2 (A), L1.2, R1.1
EXT_VIN_SW: C1.2, D3.1 (K), IC2.6 (SW), L1.1
GND: C3.1, C4.1, C5.2, C6.1, C7.1, C8.1, C9.1, C10.1, C11.1, C16.2 (-), C17.2 (-), C18.1, C19.1, C20.1, C21.1, D2.2, D3.2 (A), D4.1, D5.2, D6.2, D7.2, D8.2, D9.2, D10.1 (A), D11.2, D12.2, D13.2, D14.2, IC1.2 (GND), IC2.2 (GND), IC3.2 (V-), IC4.3 (GND), IC5.5 (IMODE), IC5.7 (PGND), IC5.13 (GND), IC5.17 (EP), IC6.5 (IMODE), IC6.7 (PGND), IC6.13 (GND), IC6.17 (EP), J1.9 (GND), J1.24 (GND), J2.2, JP10.3, JP11.3, R2.2, R3.2, R8.2, R11.1, R14.2, R15.2, U1.3 (GND), Z2.2 (A)
IPROPI0: IC5.4 (IPROPI), R14.1
IPROPI1: IC6.4 (IPROPI), R15.1
NFAULT0: IC5.2 (NFAULT), R12.2
NFAULT1: IC6.2 (NFAULT), R13.2
OUT1: IC5.6 (OUT1), J2.6
OUT2: IC5.8 (OUT2), J2.5
OUT3: IC6.6 (OUT1), J2.4
OUT4: IC6.8 (OUT2), J2.3
P0_PWM: D13.1, IC5.16 (PH/IN2), JP1.2
P0_PWM_INT: J1.1 (P0/MOSI/PWM), JP1.1
P1_PWM_INT: J1.2 (P1/MISO/CANTX), JP2.1
P2_PWM_INT: J1.3 (P2/SCLK/PWM), JP3.1
P6_ADC: JP4.2, R5.2
P6_ADC_INT: J1.7 (P6/ADC), JP4.1
P7_PWM: D11.1, IC5.15 (EN/IN1), JP5.2
P7_PWM_INT: J1.11 (P7/PWM), JP5.1
P8_PWM: D12.1, IC6.15 (EN/IN1), JP6.2
P8_PWM_INT: J1.12 (P8/PWM), JP6.1
P10_FSYNC: D8.1, IC4.4 (Y), JP7.2, R7.2, U1.2 (A)
P10_FSYNC_INT: J1.14 (P10/PWM/FSYNC), JP7.1
P12_PWM: D14.1, IC6.16 (PH/IN2), JP2.2, JP3.2
PMODE0: IC5.14 (PMODE), JP10.2
PMODE1: IC6.14 (PMODE), JP11.2
SW: IC1.1 (SW), L2.2
SYNC: J2.8, JP9.2
SYNC_IN: JP9.3, R10.2
SYNC_IN_INT: D7.1, IC4.2 (A), R6.2, R10.1, Z2.1 (K)
SYNC_OUT: JP9.1, R9.2
SYNC_OUT_INT: D9.1, R9.1, U1.4 (Y)
VCC: C3.2, C10.2, D2.1, D10.2 (K), IC4.5 (VCC), IC5.1 (NSLEEP), IC6.1 (NSLEEP), J1.8 (3.3V), JP10.1, JP11.1, L2.1, R7.1, R12.1, R13.1
VCP0: C14.2, IC5.10 (VCP)
VCP1: C15.2, IC6.10 (VCP)
VIN: D1.1 (K), J1.10 (VIN)
V_BATT: C4.2, C9.2, C11.2, C18.2, C20.2, IC1.4 (VOUT), IC3.5 (V+), IC5.3 (VREF), IC6.3 (VREF), R6.1, U1.5 (VCC)

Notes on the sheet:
Copyright (c) 2013-2023 OpenMV <openmv@openmv.io>
This work is licensed under the Creative Commons Attribution-ShareAlike 3.0 License.
To view a copy of this license, visit http://creativecommons.org/licenses/by-sa/3.0/
FSYNC Input and Output
Mechanical
Shield Headers
6V to 36V Buck
3.3V to 5V Boost
H-Bridge Drivers
Terminal
ADC Input
